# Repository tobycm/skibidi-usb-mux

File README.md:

# Skibidi USB Mux

A simple USB mux with 2 upstream USB C ports and 3 downstream USB A ports and 1 downstream USB C port. Powered by the onsemi FSUSB42MUX mux and WCH CH334P usb hub IC.

## PCB

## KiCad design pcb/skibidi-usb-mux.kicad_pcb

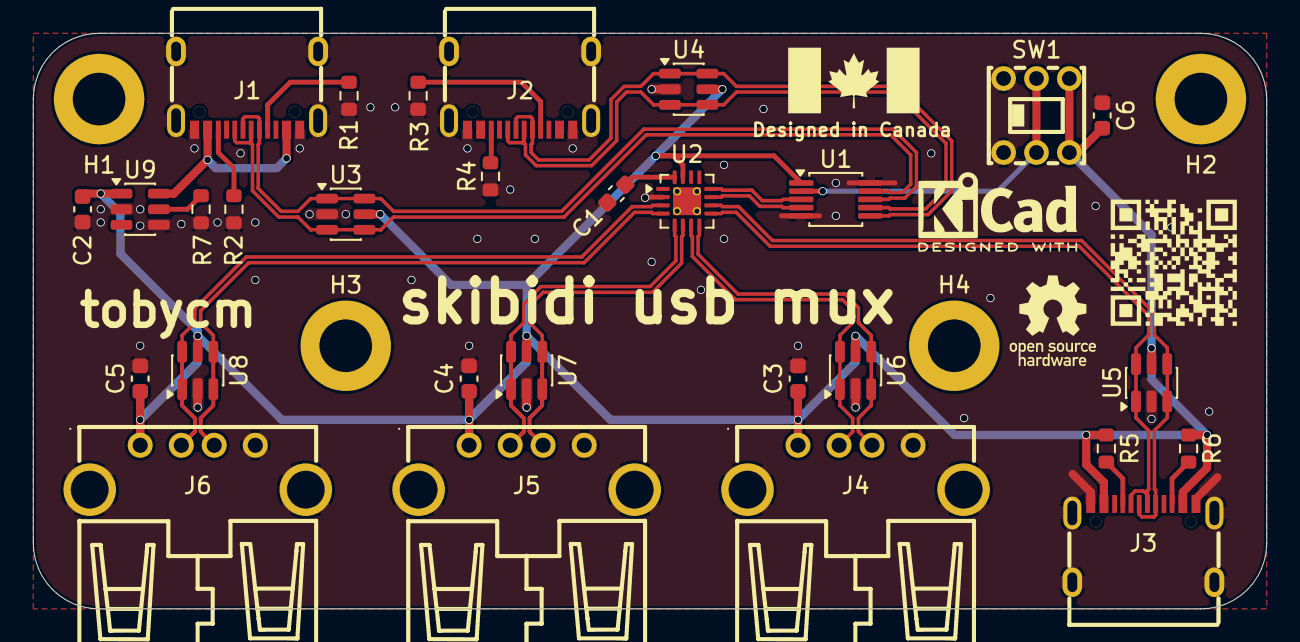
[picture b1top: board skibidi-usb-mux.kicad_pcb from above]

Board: 2 copper layers, 75.0 x 35.0 mm, 33 parts (0 on the bottom side), 26 nets.

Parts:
C1, C6: 100n; C_0603_1608Metric
C2, C3, C4, C5: 10u; C_0603_1608Metric
H1, H2, H3, H4: MountingHole; MountingHole_3.2mm_M3_ISO14580_Pad
J1, J2, J3: USB_C_Receptacle_USB2.0_14P; USB-C-SMD_TYPE-C-16PIN-2MD-073
J4, J5, J6: USB_A; USB-A-TH_AF-WJDG
R1, R2, R3, R4: 5.1k; R_0603_1608Metric
R5, R6: 56k; R_0603_1608Metric
R7: 24k; R_0603_1608Metric
SW1: PS-5850A-6PL; SW-TH_6P-L5.8-W5.8-P2.00-LS4.5-BL_1
U1: FSUSB42MUX; MSOP-10_3x3mm_P0.5mm
U2: CH334P; QFN-16-1EP_3x3mm_P0.5mm_EP1.7x1.7mm_ThermalVias
U3, U4, U5, U6, U7, U8: USBLC6-2SC6; SOT-23-6
U9: CH217A; SOT-23-6

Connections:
/1D+: J3.A6 (D+), J3.B6 (D+), U2.10 (DP1), U5.3 (I/O2), U5.4 (I/O2)
/1D-: J3.A7 (D-), J3.B7 (D-), U2.9 (DM1), U5.1 (I/O1), U5.6 (I/O1)
/2D+: J4.3 (D+), U2.8 (DP2), U6.3 (I/O2), U6.4 (I/O2)
/2D-: J4.2 (D-), U2.7 (DM2), U6.1 (I/O1), U6.6 (I/O1)
/3D+: J5.3 (D+), U2.6 (DP3), U7.3 (I/O2), U7.4 (I/O2)
/3D-: J5.2 (D-), U2.5 (DM3), U7.1 (I/O1), U7.6 (I/O1)
/4D+: J6.3 (D+), U2.4 (DP4), U8.3 (I/O2), U8.4 (I/O2)
/4D-: J6.2 (D-), U2.3 (DM4), U8.1 (I/O1), U8.6 (I/O1)
/SEL: SW1.2, SW1.5, U1.2 (SEL)
/U1D+: J2.A6 (D+), J2.B6 (D+), U1.7 (HSD1+), U4.3 (I/O2), U4.4 (I/O2)
/U1D-: J2.A7 (D-), J2.B7 (D-), U1.6 (HSD1-), U4.1 (I/O1), U4.6 (I/O1)
/U2D+: J1.A6 (D+), J1.B6 (D+), U1.9 (HSD2+), U3.3 (I/O2), U3.4 (I/O2)
/U2D-: J1.A7 (D-), J1.B7 (D-), U1.8 (HSD2-), U3.1 (I/O1), U3.6 (I/O1)
/UD+: U1.3 (D+), U2.12 (DPU)
/UD-: U1.4 (D-), U2.11 (DMU)
GND: C1.1, C2.1, C3.1, C4.1, C5.1, C6.1, J1.A1 (GND), J1.B1 (GND), J1.SH (SHIELD), J2.A1 (GND), J2.B1 (GND), J2.SH (SHIELD), J3.A1 (GND), J3.B1 (GND), J3.SH (SHIELD), J4.4 (GND), J4.SH (Shield), J5.4 (GND), J5.SH (Shield), J6.4 (GND), J6.SH (Shield), R1.1, R2.1, R3.1, R4.1, R7.1, SW1.1, SW1.4, U1.5 (GND), U1.10 (~OE), U2.2 (XI), U2.17 (GND), U3.2 (GND), U4.2 (GND), U5.2 (GND), U6.2 (GND), U7.2 (GND), U8.2 (GND), U9.2 (GND), U9.4 (EN#)
unnamed: J1.A5 (CC1), R1.2
unnamed: J1.B5 (CC2), R2.2
unnamed: J2.A5 (CC1), R3.2
unnamed: J2.B5 (CC2), R4.2
unnamed: J3.A5 (CC1), R5.2
unnamed: J3.B5 (CC2), R6.2
unnamed: C1.2, U2.16 (VDD33)
unnamed: R7.2, U9.5 (ISET)
unnamed: J1.A4 (VBUS), J1.B4 (VBUS), U9.6 (VIN)
VBUS: C2.2, C3.2, C4.2, C5.2, C6.2, J3.A4 (VBUS), J3.B4 (VBUS), J4.1 (VBUS), J5.1 (VBUS), J6.1 (VBUS), R5.1, R6.1, SW1.3, SW1.6, U1.1 (VCC), U2.15 (V5), U3.5 (VBUS), U4.5 (VBUS), U5.5 (VBUS), U6.5 (VBUS), U7.5 (VBUS), U8.5 (VBUS), U9.1 (VOUT)

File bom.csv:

Description,Quantity,Part #,Unit price,Extended Price USD,Product Link
100nF ±10% 50V Ceramic Capacitor X7R 0603,50,CC0603KRX7R9BB104,0.0175,0.88,https://www.lcsc.com/product-detail/C14663.html
10uF ±20% 25V Ceramic Capacitor X5R 0603,60,CL10A106MA8NRNC,0.0798,4.79,https://www.lcsc.com/product-detail/C96446.html
"USB-C (USB TYPE-C) Receptacle Connector 16 Position Surface Mount, Right Angle",40,TYPE-C 16PIN 2MD(073),0.0707,2.83,https://www.lcsc.com/product-detail/C2765186.html
USB-A (USB TYPE-A) Receptacle Connector 4 Position Right Angle,30,AF 90 WJDG,0.0487,1.46,https://www.lcsc.com/product-detail/C456018.html
5.1k? ±1% 100mW 0603 Thick Film Resistor,100,FRC0603F5101TS,0.0025,0.25,https://www.lcsc.com/product-detail/C2907044.html
56k? ±1% 100mW 0603 Thick Film Resistor,100,0603WAF5602T5E,0.005,0.50,https://www.lcsc.com/product-detail/C23206.html
Pushbutton Switch DPDT Rectangular Plunger,10,PS-5850A-6PL,0.2048,2.05,https://www.lcsc.com/product-detail/C963201.html
3V~4.4V 720MHz 3.9? 2:1 MSOP-10 Analog Switches - Special Purpose RoHS,10,FSUSB42MUX,0.3187,3.19,https://www.lcsc.com/product-detail/C11355.html
4 480Mbps USB 2.0 QFN-16(3x3) Interface Controllers RoHS,10,CH334P,0.3658,3.66,https://www.lcsc.com/product-detail/C5373042.html
12VC Clamp 6A Ipp ESD DIODE SOT-23-6,100,USBLC6-2SC6,0.0355,3.55,https://www.lcsc.com/product-detail/C2827654.html
24k? ±1% 100mW 0603 Thick Film Resistor,100,FRC0603F2402TS,0.0027,0.27,https://www.lcsc.com/product-detail/C2930081.html
,,,,,
LCSC Shipping,,LCSC Shipping,12.62,12.62,https://www.lcsc.com/
PCB,,PCB,5,5,https://jlcpcb.com/
Stencil,,Stencil,3.07,3.07,https://jlcpcb.com/
JLCPCB Shipping,,JLCPCB Shipping,9.5,9.5,https://jlcpcb.com/
,,,,,
,,Total:,,53.61,
